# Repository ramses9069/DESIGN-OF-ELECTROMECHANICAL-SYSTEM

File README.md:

# -DESIGN-OF-ELECTROMECHANICAL-SYSTEMS
A REPOSITORY CONTAINING DESIGN PROJECTS

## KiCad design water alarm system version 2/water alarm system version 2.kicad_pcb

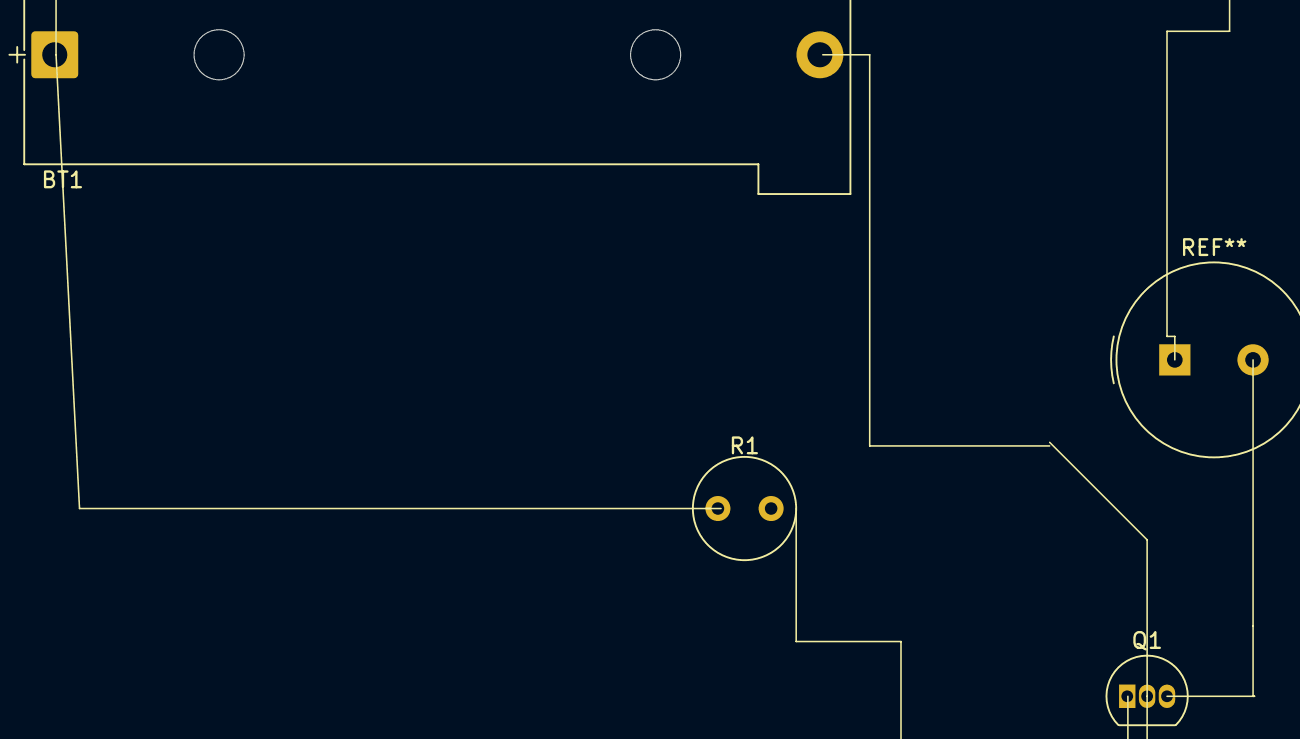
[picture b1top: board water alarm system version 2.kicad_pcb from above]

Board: 2 copper layers, 3 parts (0 on the bottom side), 2 nets, no tracks yet.

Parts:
BT1: 12v; BatteryHolder_Bulgin_BX0034_1xAAA
Q1: 2N3904; TO-92_Inline
R1: 100k; R_LDR_D6.4mm_P3.4mm_Vertical

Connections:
Earth: BT1.2 (-), Q1.1 (E)
unnamed: BT1.1 (+), R1.1

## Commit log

2025-11-03 Update Circuit Board
2026-02-02 Fix typo in README description
